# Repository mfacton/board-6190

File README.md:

# pcb-6190
PCB to replace sus breadboards in 6.190 MIT class - programming in c and assembly

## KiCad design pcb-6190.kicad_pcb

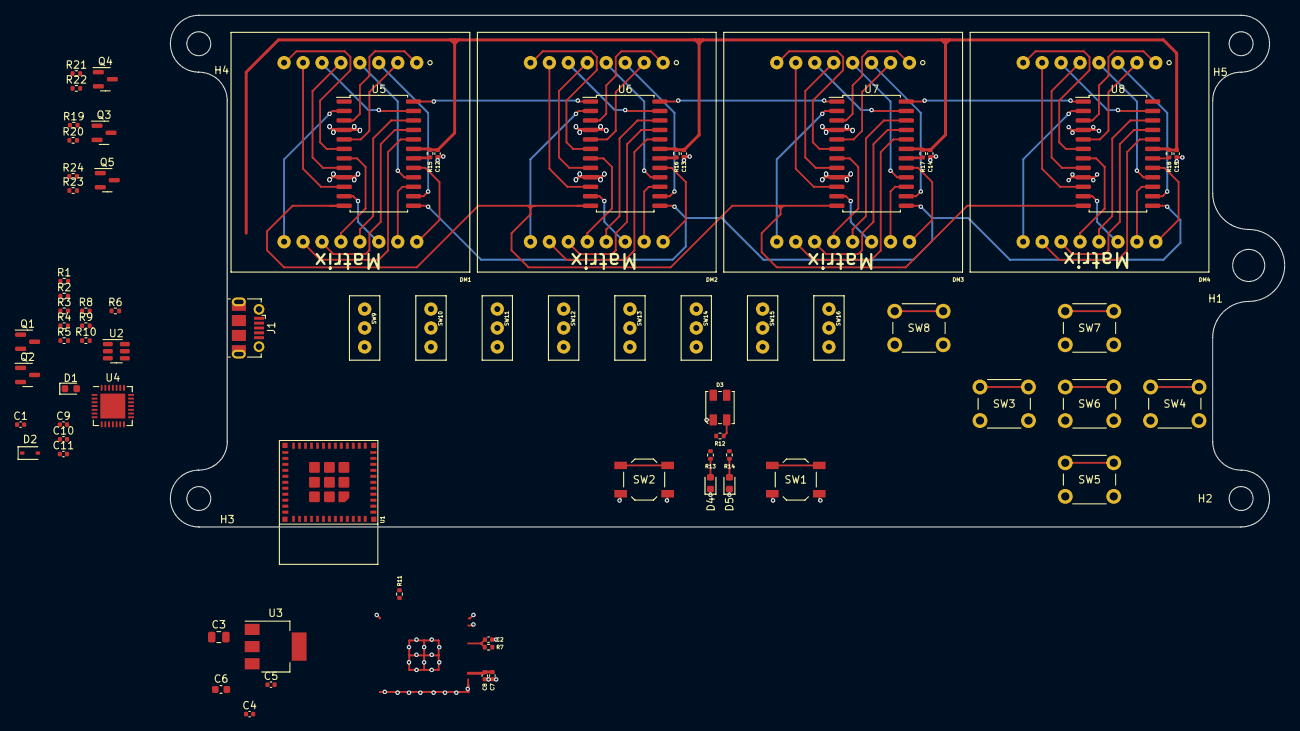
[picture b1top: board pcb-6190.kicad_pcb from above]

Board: 4 copper layers, 149.4 x 68.6 mm, 83 parts (0 on the bottom side), 109 nets.

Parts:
C1, C2, C10: 1u; C_0402_1005Metric
C3: 22u; C_0805_2012Metric
C4, C5, C8, C11, C12, C13, C14, C15: 100n; C_0402_1005Metric
C6: 22u; C_0603_1608Metric
C7, C9: 10u; C_0402_1005Metric
D1, D4, D5: LED; LED_0603_1608Metric
D2: 1N5819WS; D_SOD-323
D3: SK6812MINI-HS
DM1, DM2, DM3, DM4: LED_8x8
H1: MountingHole; MountingHole_4.3mm_M4
H2, H3, H4, H5: MountingHole; MountingHole_3.2mm_M3
J1: USB_B_Micro; USB_Micro-B_Molex-105017-0001
Q1, Q2: MMBT3904; SOT-23
Q3, Q4, Q5: AO3400A; SOT-23
R1: 5k; R_0402_1005Metric
R2, R3, R7, R8, R11, R15, R16, R17, R18: 10k; R_0402_1005Metric
R4: 22k; R_0402_1005Metric
R5: 47k; R_0402_1005Metric
R6: 1k; R_0402_1005Metric
R9, R10, R12: 0; R_0402_1005Metric
R13, R14: 500; R_0402_1005Metric
R19, R20, R21, R22, R23, R24: 4.7k; R_0402_1005Metric
SW1, SW2: SW_Push; SW_SPST_TL3342
SW3, SW4, SW5, SW6, SW7, SW8: SW_Push; SW_PUSH_6mm
SW9, SW10, SW11, SW12, SW13, SW14, SW15, SW16: SW_SPDT; SPDT_Slide_SS12D00G
U1: ESP32-C3-MINI-1
U2: SRV05-4; SOT-23-6
U3: AMS1117-3.3; SOT-223-3_TabPin2
U4: CP2102N-Axx-xQFN28; QFN-28-1EP_5x5mm_P0.5mm_EP3.35x3.35mm
U5, U6, U7, U8: MAX7221xWG; SOIC-24W_7.5x15.4mm_P1.27mm

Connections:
+3.3V: C5.1, C6.1, C7.1, C8.1, C9.1, C11.1, D3.3 (VDD), Q3.1 (G), Q4.1 (G), Q5.1 (G), R6.2, R7.1, R11.1, R20.1, R21.1, R23.1, U1.3 (3V3), U3.2 (VO), U4.6 (VDD), U4.7 (VREGIN)
+5V: C1.1, C3.1, C4.1, C12.1, C13.1, C14.1, C15.1, D2.1 (K), R1.1, R15.1, R16.1, R17.1, R18.1, R19.1, R22.1, R24.1, U3.3 (VI), U5.19 (V+), U6.19 (V+), U7.19 (V+), U8.19 (V+)
/CLK: Q4.3 (D), R22.2, U5.12 (~CS), U6.12 (~CS), U7.12 (~CS), U8.12 (~CS)
/CS: Q3.3 (D), R19.2, U5.13 (CLK), U6.13 (CLK), U7.13 (CLK), U8.13 (CLK)
/DIN: Q5.3 (D), R24.2, U5.1 (DIN)
/DTR: Q2.2 (E), R2.1, U4.28 (~DTR)
/EN: C2.1, Q1.3 (C), R7.2, SW2.1, U1.8 (EN)
/IO0: Q4.2 (S), R21.2, U1.12 (IO0)
/IO1: Q3.2 (S), R20.2, U1.13 (IO1)
/IO2: R14.1, U1.5 (IO2)
/IO3: R13.1, U1.6 (IO3)
/IO4: SW3.1, SW14.2 (B), U1.18 (IO4)
/IO5: SW4.1, SW13.2 (B), U1.19 (IO5)
/IO6: SW5.1, SW12.2 (B), U1.20 (IO6)
/IO7: SW6.1, SW11.2 (B), U1.21 (IO7)
/IO8: R11.2, R12.1, SW7.1, SW10.2 (B), U1.22 (IO8)
/IO9: Q2.3 (C), SW1.1, SW8.1, SW9.2 (B), U1.23 (IO9)
/IO10: Q5.2 (S), R23.2, U1.16 (IO10)
/IO18: SW15.2 (B), U1.26 (IO18)
/IO19: SW16.2 (B), U1.27 (IO19)
/Matrix1/C1: DM1.13 (C1), U5.22 (SEG_DP)
/Matrix1/C2: DM1.3 (C2), U5.14 (SEG_A)
/Matrix1/C3: DM1.4 (C3), U5.16 (SEG_B)
/Matrix1/C4: DM1.10 (C4), U5.20 (SEG_C)
/Matrix1/C5: DM1.6 (C5), U5.23 (SEG_D)
/Matrix1/C6: DM1.11 (C6), U5.21 (SEG_E)
/Matrix1/C7: DM1.15 (C7), U5.15 (SEG_F)
/Matrix1/C8: DM1.16 (C8), U5.17 (SEG_G)
/Matrix1/DOUT: U5.24 (DOUT), U6.1 (DIN)
/Matrix1/R1: DM1.9 (R1), U5.2 (DIG_0)
/Matrix1/R2: DM1.14 (R2), U5.11 (DIG_1)
/Matrix1/R3: DM1.8 (R3), U5.6 (DIG_2)
/Matrix1/R4: DM1.12 (R4), U5.7 (DIG_3)
/Matrix1/R5: DM1.1 (R5), U5.3 (DIG_4)
/Matrix1/R6: DM1.7 (R6), U5.10 (DIG_5)
/Matrix1/R7: DM1.2 (R7), U5.5 (DIG_6)
/Matrix1/R8: DM1.5 (R8), U5.8 (DIG_7)
/Matrix2/C1: DM2.13 (C1), U6.22 (SEG_DP)
/Matrix2/C2: DM2.3 (C2), U6.14 (SEG_A)
/Matrix2/C3: DM2.4 (C3), U6.16 (SEG_B)
/Matrix2/C4: DM2.10 (C4), U6.20 (SEG_C)
/Matrix2/C5: DM2.6 (C5), U6.23 (SEG_D)
/Matrix2/C6: DM2.11 (C6), U6.21 (SEG_E)
/Matrix2/C7: DM2.15 (C7), U6.15 (SEG_F)
/Matrix2/C8: DM2.16 (C8), U6.17 (SEG_G)
/Matrix2/DOUT: U6.24 (DOUT), U7.1 (DIN)
/Matrix2/R1: DM2.9 (R1), U6.2 (DIG_0)
/Matrix2/R2: DM2.14 (R2), U6.11 (DIG_1)
/Matrix2/R3: DM2.8 (R3), U6.6 (DIG_2)
/Matrix2/R4: DM2.12 (R4), U6.7 (DIG_3)
/Matrix2/R5: DM2.1 (R5), U6.3 (DIG_4)
/Matrix2/R6: DM2.7 (R6), U6.10 (DIG_5)
/Matrix2/R7: DM2.2 (R7), U6.5 (DIG_6)
/Matrix2/R8: DM2.5 (R8), U6.8 (DIG_7)
/Matrix3/C1: DM3.13 (C1), U7.22 (SEG_DP)
/Matrix3/C2: DM3.3 (C2), U7.14 (SEG_A)
/Matrix3/C3: DM3.4 (C3), U7.16 (SEG_B)
/Matrix3/C4: DM3.10 (C4), U7.20 (SEG_C)
/Matrix3/C5: DM3.6 (C5), U7.23 (SEG_D)
/Matrix3/C6: DM3.11 (C6), U7.21 (SEG_E)
/Matrix3/C7: DM3.15 (C7), U7.15 (SEG_F)
/Matrix3/C8: DM3.16 (C8), U7.17 (SEG_G)
/Matrix3/DOUT: U7.24 (DOUT), U8.1 (DIN)
/Matrix3/R1: DM3.9 (R1), U7.2 (DIG_0)
/Matrix3/R2: DM3.14 (R2), U7.11 (DIG_1)
/Matrix3/R3: DM3.8 (R3), U7.6 (DIG_2)
/Matrix3/R4: DM3.12 (R4), U7.7 (DIG_3)
/Matrix3/R5: DM3.1 (R5), U7.3 (DIG_4)
/Matrix3/R6: DM3.7 (R6), U7.10 (DIG_5)
/Matrix3/R7: DM3.2 (R7), U7.5 (DIG_6)
/Matrix3/R8: DM3.5 (R8), U7.8 (DIG_7)
/Matrix4/C1: DM4.13 (C1), U8.22 (SEG_DP)
/Matrix4/C2: DM4.3 (C2), U8.14 (SEG_A)
/Matrix4/C3: DM4.4 (C3), U8.16 (SEG_B)
/Matrix4/C4: DM4.10 (C4), U8.20 (SEG_C)
/Matrix4/C5: DM4.6 (C5), U8.23 (SEG_D)
/Matrix4/C6: DM4.11 (C6), U8.21 (SEG_E)
/Matrix4/C7: DM4.15 (C7), U8.15 (SEG_F)
/Matrix4/C8: DM4.16 (C8), U8.17 (SEG_G)
/Matrix4/R1: DM4.9 (R1), U8.2 (DIG_0)
/Matrix4/R2: DM4.14 (R2), U8.11 (DIG_1)
/Matrix4/R3: DM4.8 (R3), U8.6 (DIG_2)
/Matrix4/R4: DM4.12 (R4), U8.7 (DIG_3)
/Matrix4/R5: DM4.1 (R5), U8.3 (DIG_4)
/Matrix4/R6: DM4.7 (R6), U8.10 (DIG_5)
/Matrix4/R7: DM4.2 (R7), U8.5 (DIG_6)
/Matrix4/R8: DM4.5 (R8), U8.8 (DIG_7)
/NSPD: R8.2, U4.11 (~SUSPEND)
/PGH: Q1.1 (B), R2.2
/PGL: Q2.1 (B), R3.2
/RGB: D3.2 (DIN), R12.2
/RSTPG: R6.1, U4.9 (~RST)
/RTS: Q1.2 (E), R3.1, U4.24 (~RTS)
/RXD0: R9.1, U1.30 (RXD0)
/RXPG: R10.2, U4.25 (RXD)
/TXD0: R10.1, U1.31 (TXD0)
/TXPG: R9.2, U4.26 (TXD)
/USB_D+: J1.3 (D+), U2.3 (IO2), U4.4 (D+)
/USB_D-: J1.2 (D-), U2.1 (IO1), U4.5 (D-)
/VBLED: D1.2 (A), R1.2
/VBUSFT: C10.1, R4.1, R5.2, U4.8 (VBUS)
GND: C1.2, C2.2, C3.2, C4.2, C5.2, C6.2, C7.2, C8.2, C9.2, C10.2, C11.2, C12.2, C13.2, C14.2, C15.2, D1.1 (K), D3.1 (GND), D4.1 (K), D5.1 (K), J1.5 (GND), J1.6 (Shield), R5.1, R8.1, SW1.2, SW2.2, SW3.2, SW4.2, SW5.2, SW6.2, SW7.2, SW8.2, SW9.1 (A), SW10.1 (A), SW11.1 (A), SW12.1 (A), SW13.1 (A), SW14.1 (A), SW15.1 (A), SW16.1 (A), U1.1 (GND), U1.2 (GND), U1.11 (GND), U1.14 (GND), U1.36 (GND), U1.37 (GND), U1.38 (GND), U1.39 (GND), U1.40 (GND), U1.41 (GND), U1.42 (GND), U1.43 (GND), U1.44 (GND), U1.45 (GND), U1.46 (GND), U1.47 (GND), U1.48 (GND), U1.49 (PGND), U1.50 (GND), U1.51 (GND), U1.52 (GND), U1.53 (GND), U2.2 (VN), U3.1 (GND), U4.3 (GND), U4.29 (GND), U5.4 (GND), U5.9 (GND), U6.4 (GND), U6.9 (GND), U7.4 (GND), U7.9 (GND), U8.4 (GND), U8.9 (GND)
unnamed: D4.2 (A), R13.2
unnamed: D5.2 (A), R14.2
unnamed: R15.2, U5.18 (ISET)
unnamed: R16.2, U6.18 (ISET)
unnamed: R17.2, U7.18 (ISET)
unnamed: R18.2, U8.18 (ISET)
VBUS: D2.2 (A), J1.1 (VBUS), R4.2, U2.5 (VP)

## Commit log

2024-10-20 Transfer project
